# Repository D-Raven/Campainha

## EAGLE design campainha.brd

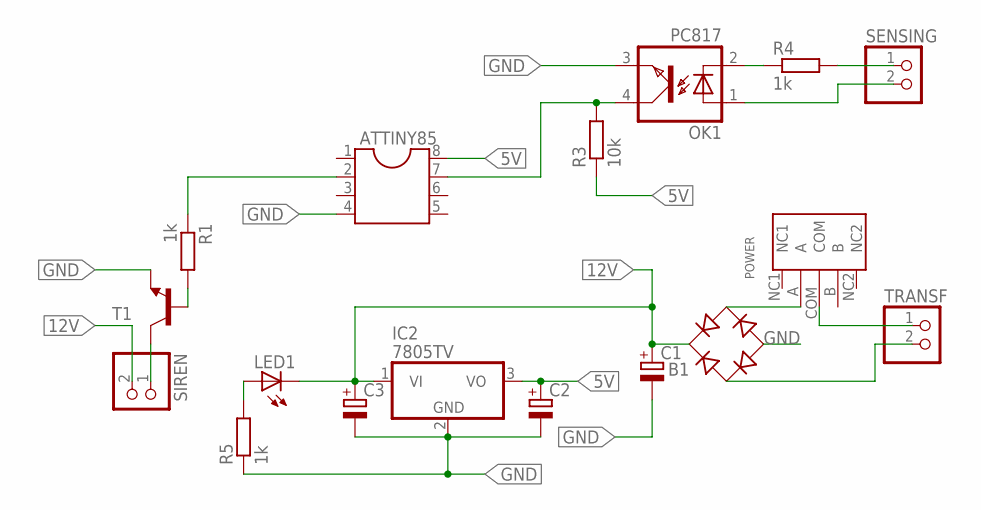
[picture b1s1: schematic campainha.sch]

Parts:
ATTINY85: DIL8S; SOCKET-08
B1: DBDB104G; DB
C1: CPOL-EUE2,5-6E; E2,5-6E
C2, C3: CPOL-EUE1.8-4; E1,8-4
IC2: 7805TV; TO220V
LED1: LED3MM
OK1: PC817; DIL04
POWER: SWITCH-2H-3P-REINFORCE; 3P-2CH-2.0-8.8X4.4X4.7H-90D-REINFORCE
R1, R4, R5: 1k; 0204/7
R3: 10k; 0204/7
SENSING: PINHD-1X2; 1X02
SIREN: PINHD-1X2; 1X02
T1: TRANSISTOR_NPNTO92; TO-92
TRANSF: PINHD-1X2; 1X02

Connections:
5V: ATTINY85.8, C2.+, IC2.3 (VO), R3.1
12V: B1.+, C1.+, C3.+, IC2.1 (VI), LED1.K (C), SIREN.2
GND: ATTINY85.4, B1.-, C1.-, C2.-, C3.-, IC2.2 (GND), OK1.3 (EMIT), R5.1, T1.1 (E)
unnamed: OK1.2 (C), R4.1
unnamed: R4.2, SENSING.1
unnamed: OK1.1 (A), SENSING.2
unnamed: ATTINY85.7, OK1.4 (COL), R3.2
unnamed: B1.AC2, POWER.A
unnamed: POWER.COM, TRANSF.1
unnamed: B1.AC1, TRANSF.2
unnamed: ATTINY85.2, R1.1
unnamed: R1.2, T1.2 (B)
unnamed: SIREN.1, T1.3 (C)
unnamed: LED1.A, R5.2

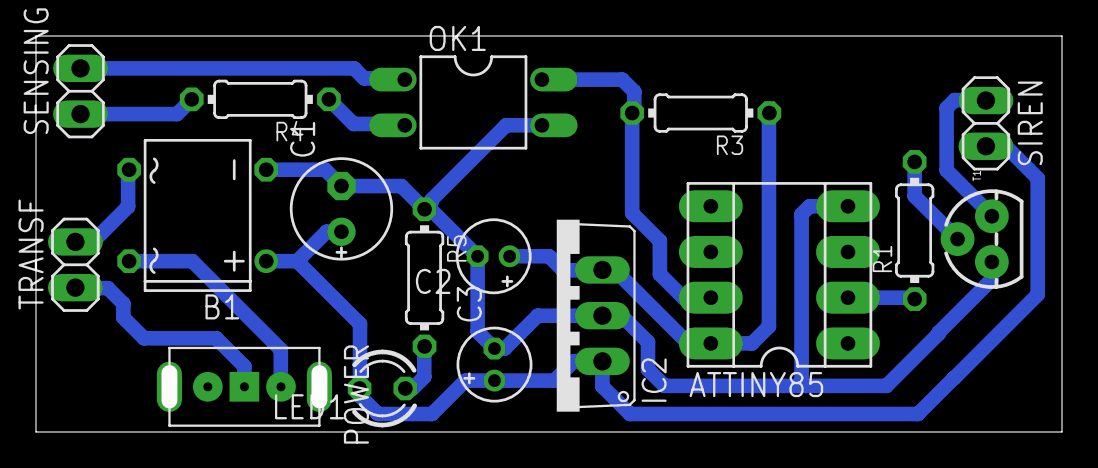
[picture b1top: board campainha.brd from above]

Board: 2 copper layers, 56.1 x 21.1 mm, 17 parts (0 on the bottom side), 14 nets.

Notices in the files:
parts and their libraries:
SparkFun-DiscreteSemi: Licensing: CC v3.0 Share-Alike You are welcome to use this library for commercial purposes.
